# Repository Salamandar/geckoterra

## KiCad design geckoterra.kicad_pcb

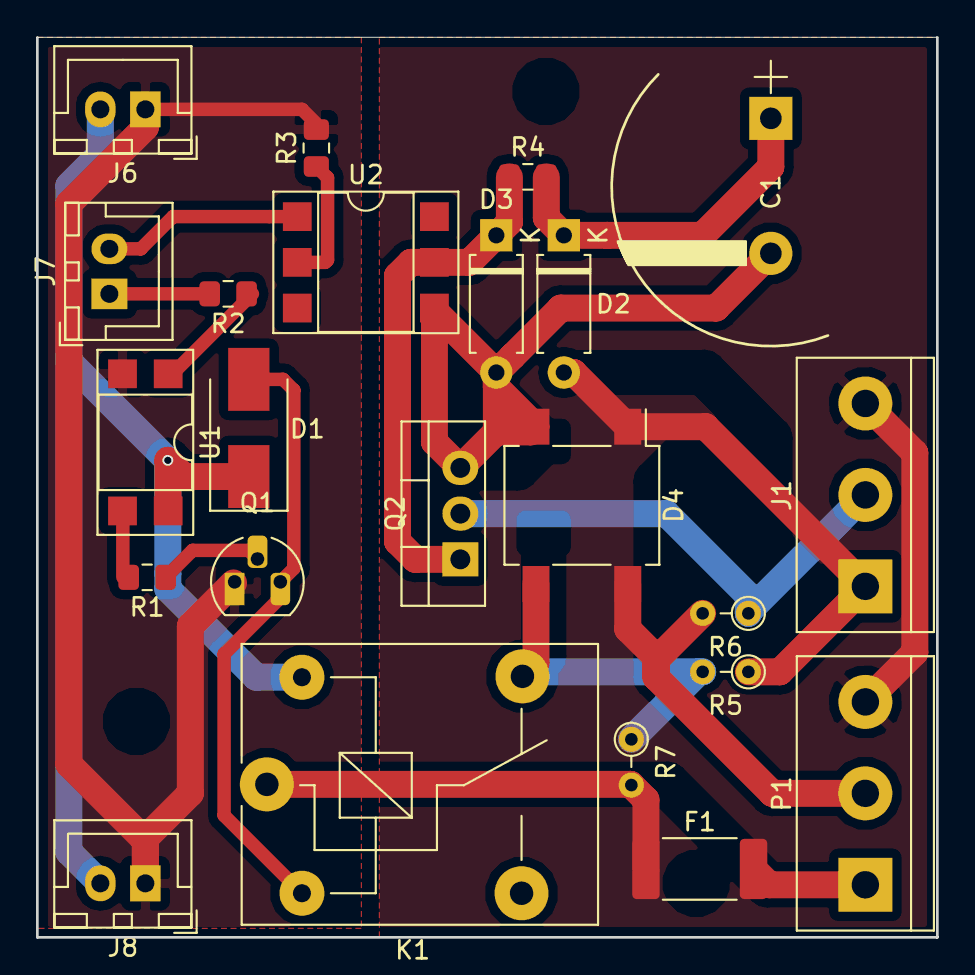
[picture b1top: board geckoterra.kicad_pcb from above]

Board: 2 copper layers, 50.0 x 50.0 mm, 23 parts (0 on the bottom side), 19 nets.

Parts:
C1: 100u; CP_Radial_D18.0mm_P7.50mm
D1: D; D_SMB_Handsoldering
D2: D_ALT; D_A-405_P7.62mm_Horizontal
D3: D_Zener_ALT; D_A-405_P7.62mm_Horizontal
D4: D_Bridge_+A-A; Diode_Bridge_Vishay_DFS
F1: Fuse; Fuse_2512_6332Metric_Pad1.52x3.35mm_HandSolder
J1: AC_Output; TerminalBlock_bornier-3_P5.08mm
J6, J7, J8: Conn_01x02; JST_XH_B02B-XH-A_1x02_P2.50mm_Vertical
K1: SANYOU_SRD_Form_C; Relay_SPDT_SANYOU_SRD_Series_Form_C
P1: AC_Input; TerminalBlock_bornier-3_P5.08mm
Q1: 2N3904; TO-92_HandSolder
Q2: Q_NMOS_GDS; TO-220-3_Vertical
R1: 510R; R_0805_2012Metric_Pad1.15x1.40mm_HandSolder
R2: 1k; R_0805_2012Metric_Pad1.15x1.40mm_HandSolder
R3: 470R; R_0805_2012Metric_Pad1.15x1.40mm_HandSolder
R4: 100k; R_0805_2012Metric_Pad1.15x1.40mm_HandSolder
R5, R6, R7: Shunt; R_Axial_DIN0204_L3.6mm_D1.6mm_P2.54mm_Vertical
U1: PC817; DIP-4_W7.62mm_SMDSocket_SmallPads
U2: 4N25; DIP-6_W7.62mm_SMDSocket_SmallPads

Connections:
+5V: D1.1, J6.2, J8.2, K1.5, U1.4
/PWMPin: J7.2, U2.1
/RelayPin: J7.1, R2.2
GND: J6.1, J8.1, Q1.1, R3.2, U1.2
unnamed: C1.1, D2.1, R4.2
unnamed: C1.2, D3.2, D4.2, Q2.3, U2.4
unnamed: D1.2, K1.2, Q1.3
unnamed: D2.2, D4.1, J1.1, R5.1
unnamed: D3.1, Q2.1, R4.1, U2.5
unnamed: D4.3, K1.4, R5.2, R7.1
unnamed: D4.4, P1.2, R6.2
unnamed: F1.1, K1.1, R7.2
unnamed: F1.2, P1.1
unnamed: J1.2, Q2.2, R6.1
unnamed: J1.3, P1.3
unnamed: Q1.2, R1.1
unnamed: R1.2, U1.3
unnamed: R2.1, U1.1
unnamed: R3.1, U2.2

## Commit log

2018-02-19 fix gitignore
2018-02-19 Added schema
2018-02-19 Added footprints, did PCB. TODO optimization.
2018-02-20 Fix footprint of relay. Create a first version 5x5cm board.
2018-02-20 edge cuts
2018-03-06 Fixed sch format. Fixed libraries.
2018-03-20 Replace all jumpers with a dual switch to shortcut the dimmer if wanted.
2018-03-20 Use jumper resistors instead of a switch. update pcb.
2018-03-20 update pcb
2018-03-21 Update pcb, again. Kinda finished.
2018-03-21 Update zones
2018-03-25 Added screw holes
2018-03-26 Add some references, change TH to SMD
2018-03-26 Add urls. Add correct footprints. Change PCB to add the big capa.
2018-03-26 Ending fixes (smaller capa footprint). Sent to seeed.
2018-04-09 Add urls, buy components
2018-08-11 Update to kicad5. Fix footprints. Move a bit to give size to the capacitor.
2018-08-23 update gitignore, send to prod.
2018-09-19 Repair PCB considering footprints
2018-09-19 Add fuse
